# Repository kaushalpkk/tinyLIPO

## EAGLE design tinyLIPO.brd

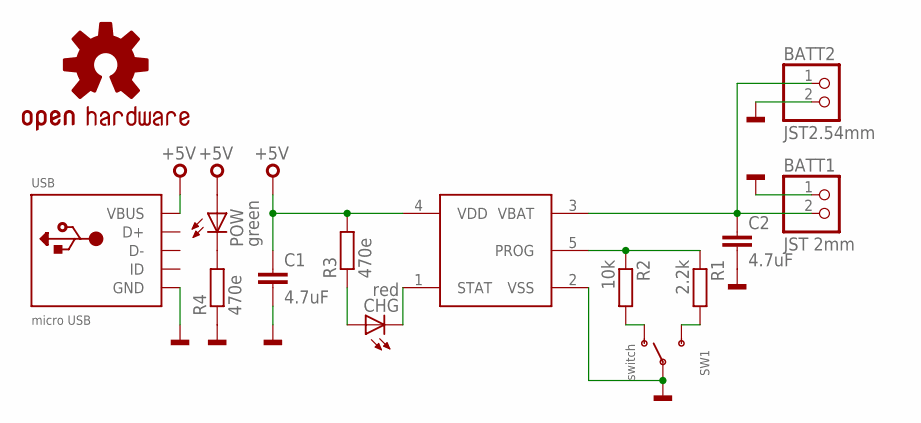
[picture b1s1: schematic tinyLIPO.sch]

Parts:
BATT1: JST 2mm; JSTPH2
BATT2: JST2.54mm; 1X02_OVAL
C1, C2: 4.7uF; C0805
CHG: red; CHIPLED_0805
IC1: MCP73831; SOT23-5
LOGO1: OSHW-LOGOM; OSHW-LOGO-M
POW: green; CHIPLED_0805
R1: 2.2k; M0805
R2: 10k; M0805
R3, R4: 470e; M0805
SW1: switch; SPDT_SMT_SSSS811101
USB: micro USB; USB-MINIB_LARGER

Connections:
+5V: C1.1, IC1.4 (VDD), POW.A, R3.2, USB.VBUS
GND: BATT1.1, BATT2.2, C1.2, C2.2, IC1.2 (VSS), R4.1, SW1.B, USB.GND
unnamed: IC1.5 (PROG), R1.1, R2.1
unnamed: R1.2, SW1.C (S)
unnamed: R2.2, SW1.A (O)
unnamed: BATT1.2, BATT2.1, C2.1, IC1.3 (VBAT)
unnamed: CHG.A, R3.1
unnamed: CHG.C, IC1.1 (STAT)
unnamed: POW.C, R4.2

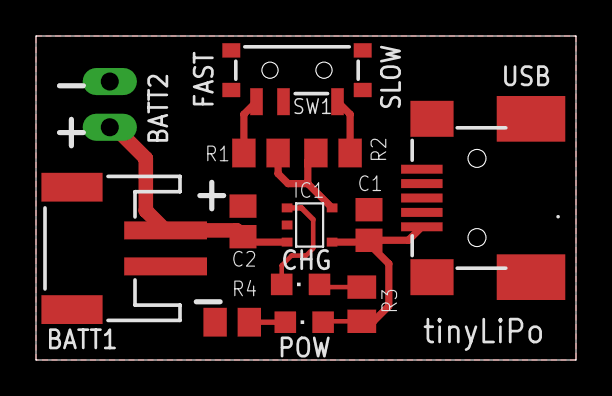
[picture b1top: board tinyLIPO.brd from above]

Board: 2 copper layers, 30.0 x 18.0 mm, 14 parts (1 on the bottom side), 9 nets.

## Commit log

2015-01-29 added gerbers, removed BOM
2015-02-13 updated gerbers for fab
2015-03-06 removed gerber schematic place adjustments added r4 r4,r3 from 220e to 470e board T.NAME adjust no DRC no ERC

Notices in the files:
parts and their libraries:
microbuilder: This work is placed in the public domain, and may be freely used for commercial and non-commercial work with the following conditions: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
SparkFun-Aesthetics: Licensing: Creative Commons ShareAlike 4.0 International - https://creativecommons.org/licenses/by-sa/4.0
